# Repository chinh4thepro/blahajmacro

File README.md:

# blahajmacro

## Info:
This board is mainly made for the purpose of having a couple of keybinds on each layer (controlled by rotary encoder(s)), and to have ease of customizability.

## Design:
The design is planned to have with a black pcb, and either laser cut acrylic pieces and/or 3d printed pieces for the case connected by M3 screws and nuts.

## Pics:

## BOM:
| Component                                       | Amount  |
|-------------------------------------------------|---------|
| Cherry MX switche (Gateron Milky Yellows)       | 4       |
| EC11 Encoder                                    | 2       |
| PCB                                             | 1       |
| Through-hole 1N4148 Diode                       | 6       |
| 0.96 inch SSD1306 OLED                          | 1       |
| M3 screws                                       | 4       |
| M3 nut                                          | 4       |
| M3 * 20 brass standoff                          | 4       |

## Mentions:
- Images:
  - blahaj outline by [Sheepy0125](https://github.com/sheepy0125)

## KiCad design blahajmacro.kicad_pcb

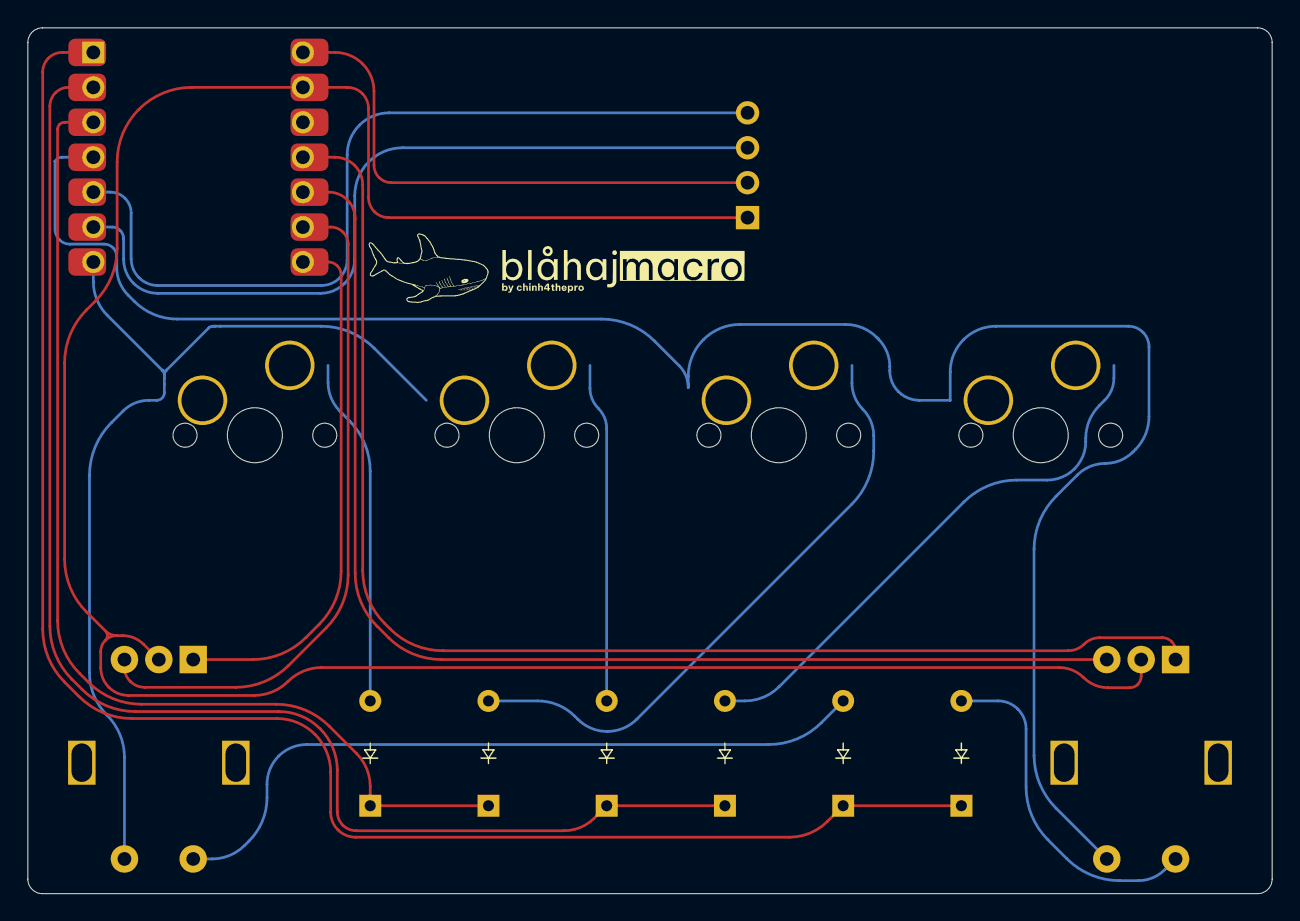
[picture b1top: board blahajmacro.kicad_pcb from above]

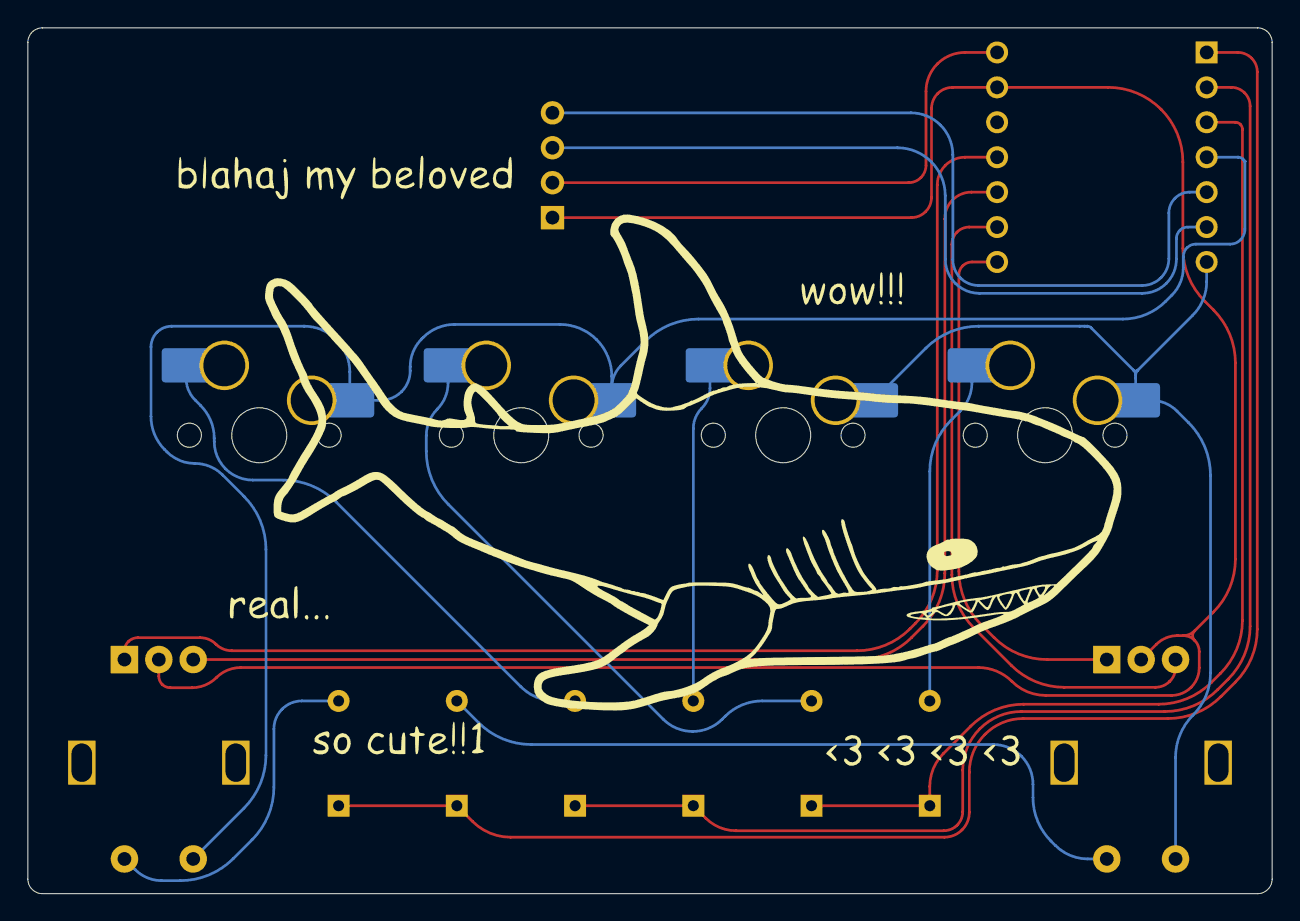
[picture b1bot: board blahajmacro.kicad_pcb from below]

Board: 2 copper layers, 90.5 x 63.0 mm, 14 parts (4 on the bottom side), 19 nets.

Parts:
D1, D2, D3, D4, D5, D6: Diode; Diode_DO-35
J1: OLED_128x32
S1, S2, S3, S4: Keyswitch; MX_Hotswap_1.00u
SW1, SW2: RotaryEncoder_Switch; Encoder_EC11_MX
U1: Seeed Studio XIAO SAMD21; Seeed_XIAO_RP2040

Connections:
+5V: J1.2 (VCC), U1.14 (5V)
COL1: S1.1, S2.1, SW1.S1, U1.7 (PB08_A6_D6_TX)
COL2: S3.1, S4.1, SW2.S1, U1.4 (PA11_A3_D3)
GND: J1.1 (GND), SW1.C, SW2.C, U1.13 (GND)
unnamed: D1.2 (A), S1.2
unnamed: D2.2 (A), S2.2
unnamed: D3.2 (A), S3.2
unnamed: D4.2 (A), S4.2
unnamed: D5.2 (A), SW1.S2
unnamed: D6.2 (A), SW2.S2
ROTA1: SW1.A, U1.8 (PB09_A7_D7_RX)
ROTA2: SW2.A, U1.11 (PA6_A10_D10_MOSI)
ROTB1: SW1.B, U1.9 (PA7_A8_D8_SCK)
ROTB2: SW2.B, U1.10 (PA5_A9_D9_MISO)
ROW1: D1.1 (K), D3.1 (K), U1.3 (PA10_A2_D2)
ROW2: D2.1 (K), D4.1 (K), U1.2 (PA4_A1_D1)
ROW3: D5.1 (K), D6.1 (K), U1.1 (PA02_A0_D0)
SCL: J1.3 (SCL), U1.6 (PA9_A5_D5_SCL)
SDA: J1.4 (SDA), U1.5 (PA8_A4_D4_SDA)

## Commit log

2024-10-03 macro...
2024-10-05 Completed pcb
2024-10-05 fix image links
2024-10-05 add on to readme
2024-10-05 add stuff for acrylic and 3d printed parts
